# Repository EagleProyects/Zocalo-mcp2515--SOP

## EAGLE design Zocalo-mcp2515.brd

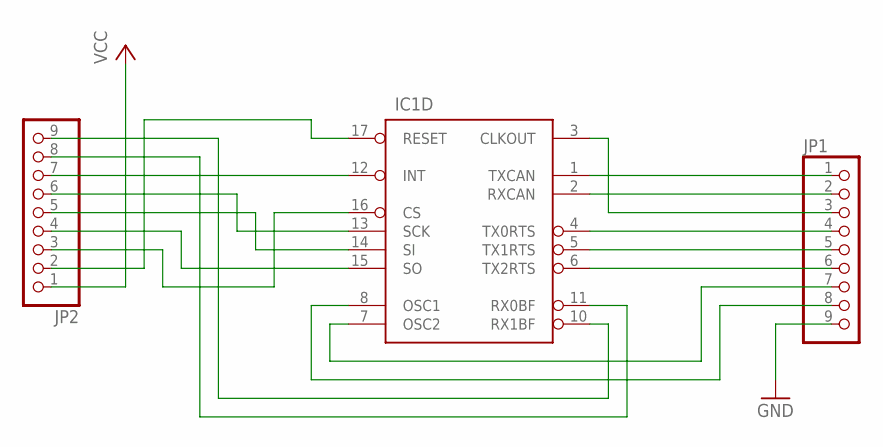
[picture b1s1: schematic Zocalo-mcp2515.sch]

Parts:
IC1: MCP2515SO; SO-18W
JP1, JP2: PINHD-1X9; 1X09

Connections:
GND: IC1.9 (GND), JP1.9
unnamed: IC1.1 (TXCAN), JP1.1
unnamed: IC1.2 (RXCAN), JP1.2
unnamed: IC1.4 (TX0RTS), JP1.4
unnamed: IC1.5 (TX1RTS), JP1.5
unnamed: IC1.6 (TX2RTS), JP1.6
unnamed: IC1.3 (CLKOUT), JP1.3
unnamed: IC1.7 (OSC2), JP1.7
unnamed: IC1.8 (OSC1), JP1.8
unnamed: IC1.10 (RX1BF), JP2.9
unnamed: IC1.11 (RX0BF), JP2.8
unnamed: IC1.12 (INT), JP2.7
unnamed: IC1.13 (SCK), JP2.6
unnamed: IC1.14 (SI), JP2.5
unnamed: IC1.15 (SO), JP2.4
unnamed: IC1.16 (CS), JP2.3
unnamed: IC1.17 (RESET), JP2.2
VCC: IC1.18 (VCC), JP2.1

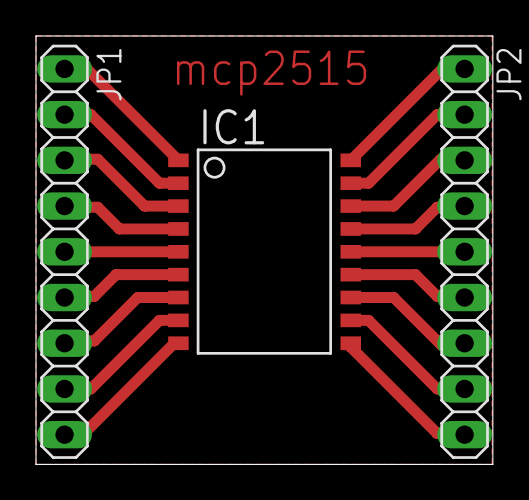
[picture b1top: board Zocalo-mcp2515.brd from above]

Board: 2 copper layers, 25.4 x 23.8 mm, 3 parts (0 on the bottom side), 18 nets.

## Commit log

2016-02-28 :tada: Added .gitattributes & .gitignore files
